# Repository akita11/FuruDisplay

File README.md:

# FuruDisplay
Versa-Writer, POV Display with scan capability

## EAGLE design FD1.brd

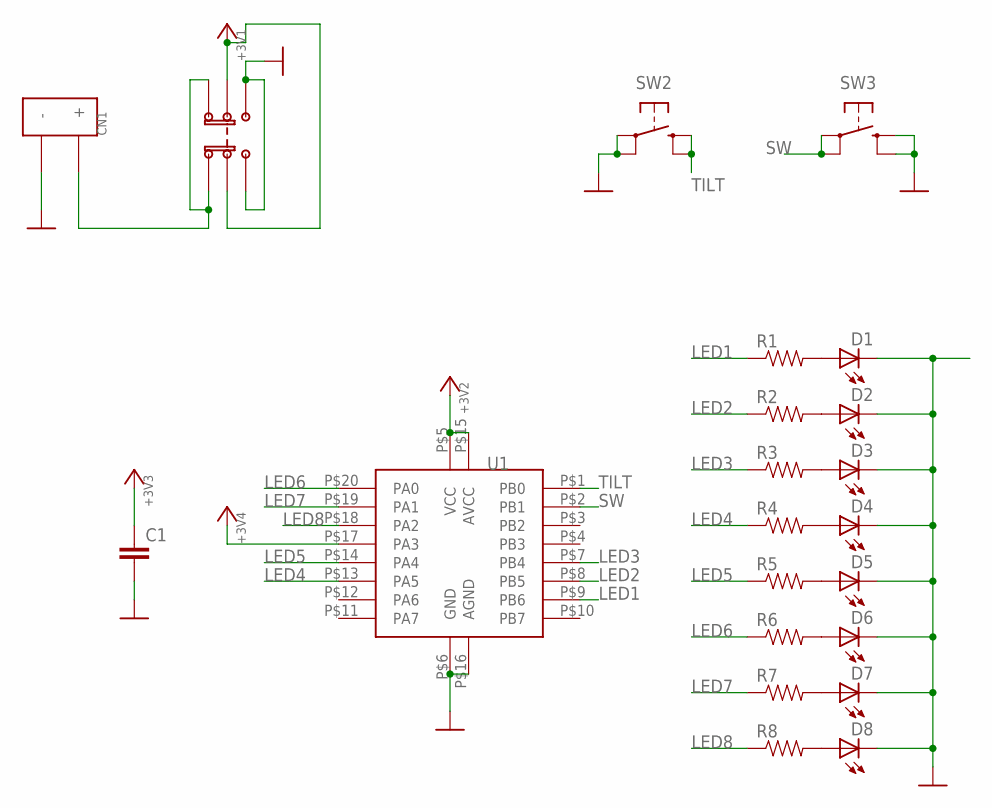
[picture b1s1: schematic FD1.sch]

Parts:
C1: CAPTH_5MML; CAP_TH_5MM_L
CN1: BAT_UM3X2
D1, D2, D3, D4, D5, D6, D7, D8: LED5MM; SPARKFUN_LED5MM
R1, R2, R3, R4, R5, R6, R7, R8: RESTH_10MML; R_TH_10MM_L
SW2: SW_TACTRBS04021-G; SW_RBS040210-G
SW3: SW_TACTTH_L; SW_TACT_L
SW4: SW_IS-1250IS2235; SW_IS2235
U1: MCU_ATTINY861PU; DIP20

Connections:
+3V3: C1.1, SW4.P$C1, SW4.P$C2, U1.P$5 (VCC), U1.P$15 (AVCC), U1.P$17 (PA3)
GND: C1.2, CN1.P$M (-), D1.K (C), D2.K (C), D3.K (C), D4.K (C), D5.K (C), D6.K (C), D7.K (C), D8.K (C), SW2.P$1, SW2.P$2 (P1), SW3.P$3 (S), SW3.P$4 (S1), SW4.P$B1, SW4.P$B2, U1.P$6 (GND), U1.P$16 (AGND)
LED1: R1.1, U1.P$9 (PB6)
LED2: R2.1, U1.P$8 (PB5)
LED3: R3.1, U1.P$7 (PB4)
LED4: R4.1, U1.P$13 (PA5)
LED5: R5.1, U1.P$14 (PA4)
LED6: R6.1, U1.P$20 (PA0)
LED7: R7.1, U1.P$19 (PA1)
LED8: R8.1, U1.P$18 (PA2)
unnamed: CN1.P$P (+), SW4.P$A1, SW4.P$A2
unnamed: D1.A, R1.2
unnamed: D2.A, R2.2
unnamed: D3.A, R3.2
unnamed: D4.A, R4.2
unnamed: D5.A, R5.2
unnamed: D6.A, R6.2
unnamed: D7.A, R7.2
unnamed: D8.A, R8.2
SW: SW3.P$1, SW3.P$2 (P1), U1.P$2 (PB1)
TILT: SW2.P$3 (S), SW2.P$4 (S1), U1.P$1 (PB0)

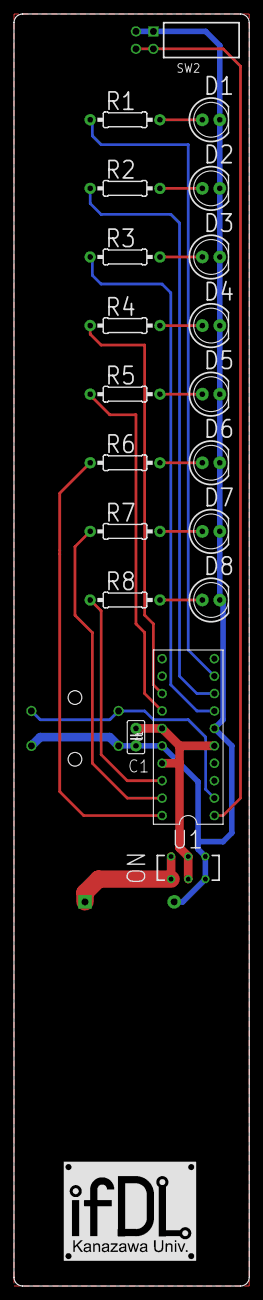
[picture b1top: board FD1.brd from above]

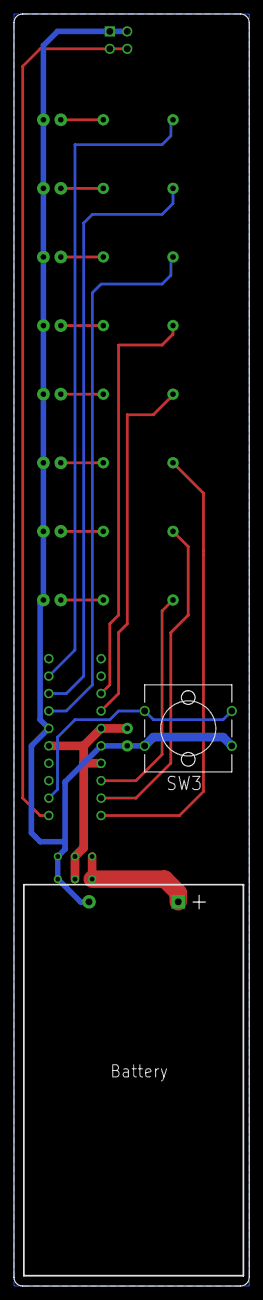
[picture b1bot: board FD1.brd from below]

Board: 2 copper layers, 34.3 x 185.4 mm, 22 parts (2 on the bottom side), 21 nets.

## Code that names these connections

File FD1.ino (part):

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#include <avr/interrupt.h>

// ATtiny861
// TILT : PB0 = D9 / PCINT8
// SW   : PB1 = D8 / PCINT9
// LED0 : PB6 = A9
// LED1 : PB5 = A8
// LED2 : PB4 = A7
// LED3 : PA5 = A4
// LED4 : PA4 = A3
// LED5 : PA0 = A0
// LED6 : PA1 = A1
// LED7 : PA2 = A2
// TXD  : PA6 = AIN0
// RXD  : PA7 = AIN1
// unused:
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void setup() {
  int i;
  uint8_t sw;
  pinMode(pinTILT, INPUT); digitalWrite(pinTILT, 1); // TILT pin, enable pullup
  pinMode(pinSW, INPUT); digitalWrite(pinSW, 1); // SW pin, enable pullup
  Serial.begin(9600); // for debug
  sw = 1; i = 0;
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
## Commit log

2019-08-07 Create LICENSE
2019-08-07 マニュアルを追記＆PDF追加
